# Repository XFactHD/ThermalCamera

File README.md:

# ThermalCamera
 Simple MLX90640 based thermal camera

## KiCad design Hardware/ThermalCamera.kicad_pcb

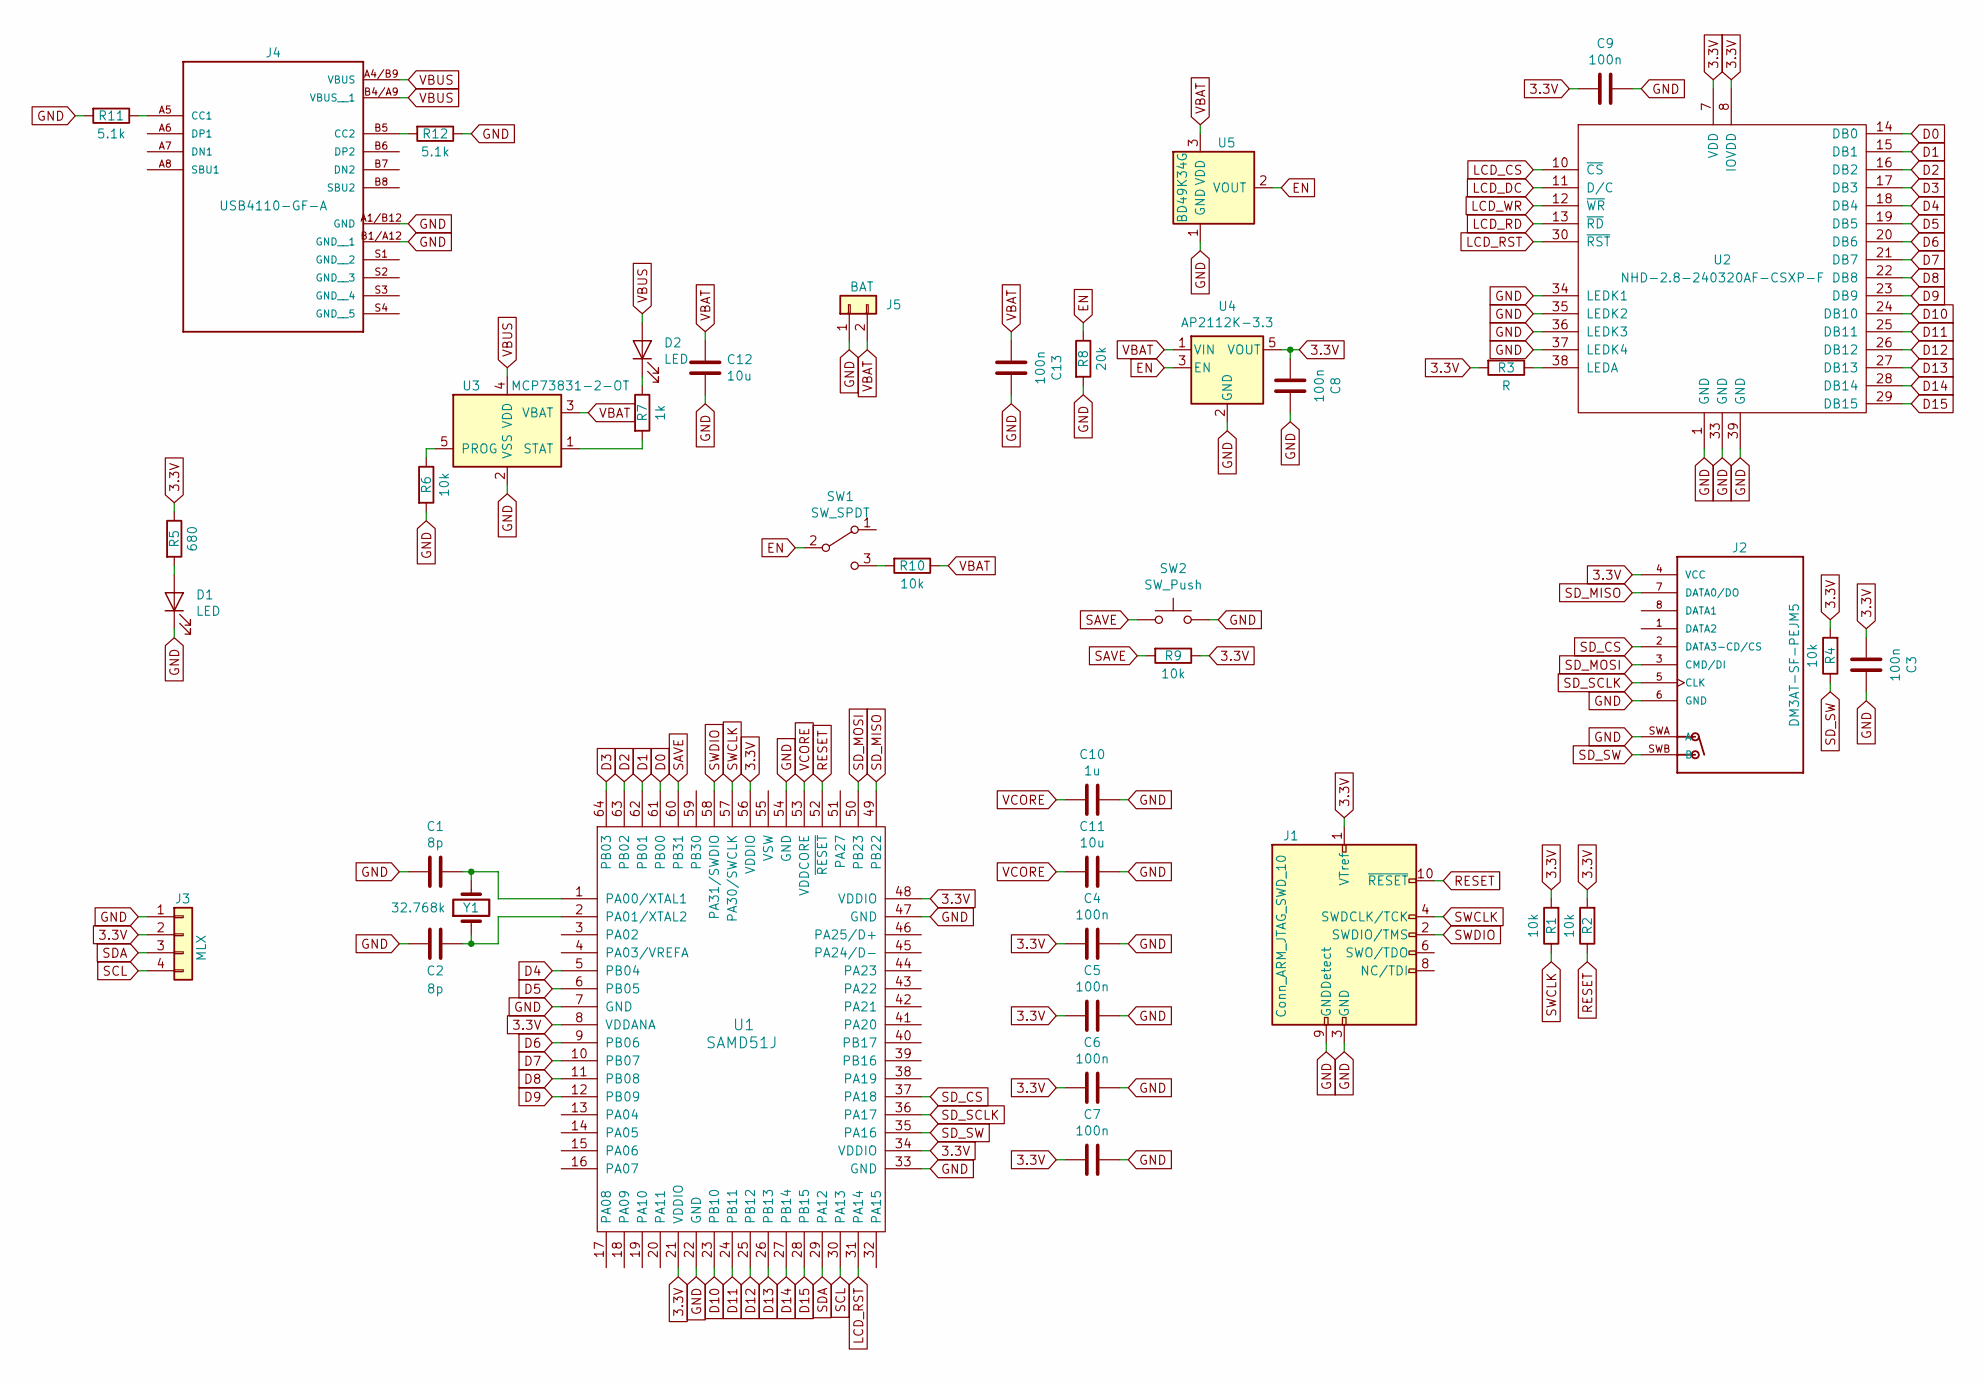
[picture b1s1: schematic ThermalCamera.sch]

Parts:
C1, C2: 8p; C_0805
C3, C4, C5, C6, C7, C8, C9, C13: 100n; C_0805
C10: 1u; C_0805
C11, C12: 10u; C_0805
D1, D2: LED; LED_0805
J1: Conn_ARM_JTAG_SWD_10; Pin_Header_Straight_2x05_Pitch1.27mm_SMD
J2: DM3AT-SF-PEJM5; HRS_DM3AT-SF-PEJM5
J3: MLX; JST_SH_SM04B-SRSS-TB_04x1.00mm_Angled
J4: USB4110-GF-A; GCT_USB4110-GF-A
J5: BAT; JST_PH_S2B-PH-SM4-TB_02x2.00mm_Angled
R1, R2, R4, R6, R9, R10: 10k; R_0805
R3: R; R_0805
R5: 680; R_0805
R7: 1k; R_0805
R8: 20k; R_0805
R11, R12: 5.1k; R_0805
SW1: SW_SPDT; SW_SPDT_PCM12
SW2: SW_Push; SW_SPST_B3U-3000P
U1: SAMD51J; TQFP-64_10x10mm_Pitch0.5mm
U2: NHD-2.8-240320AF-CSXP-F
U3: MCP73831-2-OT; SOT-23-5
U4: AP2112K-3.3; SOT-23-5
U5: BD49K34G; SOT-23
Y1: 32.768k; Crystal_SMD_3215-2pin_3.2x1.5mm

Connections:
3.3V: C3.2, C4.2, C5.2, C6.2, C7.2, C8.2, C9.2, J1.1 (VTref), J2.4 (VCC), J3.2, R1.2, R2.2, R3.2, R4.2, R5.1, R9.1, U1.8 (VDDANA), U1.21 (VDDIO), U1.34 (VDDIO), U1.48 (VDDIO), U1.56 (VDDIO), U2.7 (VDD), U2.8 (IOVDD), U4.5 (VOUT)
D0: U1.61 (PB00), U2.14 (DB0)
D1: U1.62 (PB01), U2.15 (DB1)
D2: U1.63 (PB02), U2.16 (DB2)
D3: U1.64 (PB03), U2.17 (DB3)
D4: U1.5 (PB04), U2.18 (DB4)
D5: U1.6 (PB05), U2.19 (DB5)
D6: U1.9 (PB06), U2.20 (DB6)
D7: U1.10 (PB07), U2.21 (DB7)
D8: U1.11 (PB08), U2.22 (DB8)
D9: U1.12 (PB09), U2.23 (DB9)
D10: U1.23 (PB10), U2.24 (DB10)
D11: U1.24 (PB11), U2.25 (DB11)
D12: U1.25 (PB12), U2.26 (DB12)
D13: U1.26 (PB13), U2.27 (DB13)
D14: U1.27 (PB14), U2.28 (DB14)
D15: U1.28 (PB15), U2.29 (DB15)
EN: R8.1, SW1.2 (B), U4.3 (EN), U5.2 (VOUT)
GND: C1.2, C2.2, C3.1, C4.1, C5.1, C6.1, C7.1, C8.1, C9.1, C10.1, C11.1, C12.1, C13.1, D1.1 (K), J1.3 (GND), J1.5 (GND), J1.9 (GNDDetect), J2.6 (GND), J2.SWA (A), J3.1, J4.A1/B12 (GND), J4.B1/A12 (GND__1), J5.1, R6.2, R8.2, R11.2, R12.1, SW2.2, U1.7 (GND), U1.22 (GND), U1.33 (GND), U1.47 (GND), U1.54 (GND), U2.1 (GND), U2.33 (GND), U2.34 (LEDK1), U2.35 (LEDK2), U2.36 (LEDK3), U2.37 (LEDK4), U2.39 (GND), U3.2 (VSS), U4.2 (GND), U5.1 (GND)
LCD_CS: U2.10 (~CS)
LCD_DC: U2.11 (D/C)
LCD_RD: U2.13 (~RD)
LCD_RST: U1.31 (PA14), U2.30 (~RST)
LCD_WR: U2.12 (~WR)
unnamed: C1.1, U1.1 (PA00/XTAL1), Y1.2
unnamed: C2.1, U1.2 (PA01/XTAL2), Y1.1
unnamed: D1.2 (A), R5.2
unnamed: D2.1 (K), R7.1
unnamed: J4.A5 (CC1), R11.1
unnamed: J4.B5 (CC2), R12.2
unnamed: R3.1, U2.38 (LEDA)
unnamed: R6.1, U3.5 (PROG)
unnamed: R7.2, U3.1 (STAT)
unnamed: R10.2, SW1.3 (C)
RESET: J1.10 (~RESET~), R2.1, U1.52 (~RESET)
SAVE: R9.2, SW2.1, U1.60 (PB31)
SCL: J3.4, U1.30 (PA13)
SDA: J3.3, U1.29 (PA12)
SD_CS: J2.2 (DATA3-CD/CS), U1.37 (PA18)
SD_MISO: J2.7 (DATA0/DO), U1.49 (PB22)
SD_MOSI: J2.3 (CMD/DI), U1.50 (PB23)
SD_SCLK: J2.5 (CLK), U1.36 (PA17)
SD_SW: J2.SWB (B), R4.1, U1.35 (PA16)
SWCLK: J1.4 (SWDCLK/TCK), R1.1, U1.57 (PA30/SWCLK)
SWDIO: J1.2 (SWDIO/TMS), U1.58 (PA31/SWDIO)
VBAT: C12.2, C13.2, J5.2, R10.1, U3.3 (VBAT), U4.1 (VIN), U5.3 (VDD)
VBUS: D2.2 (A), J4.A4/B9 (VBUS), J4.B4/A9 (VBUS__1), U3.4 (VDD)
VCORE: C10.2, C11.2, U1.53 (VDDCORE)

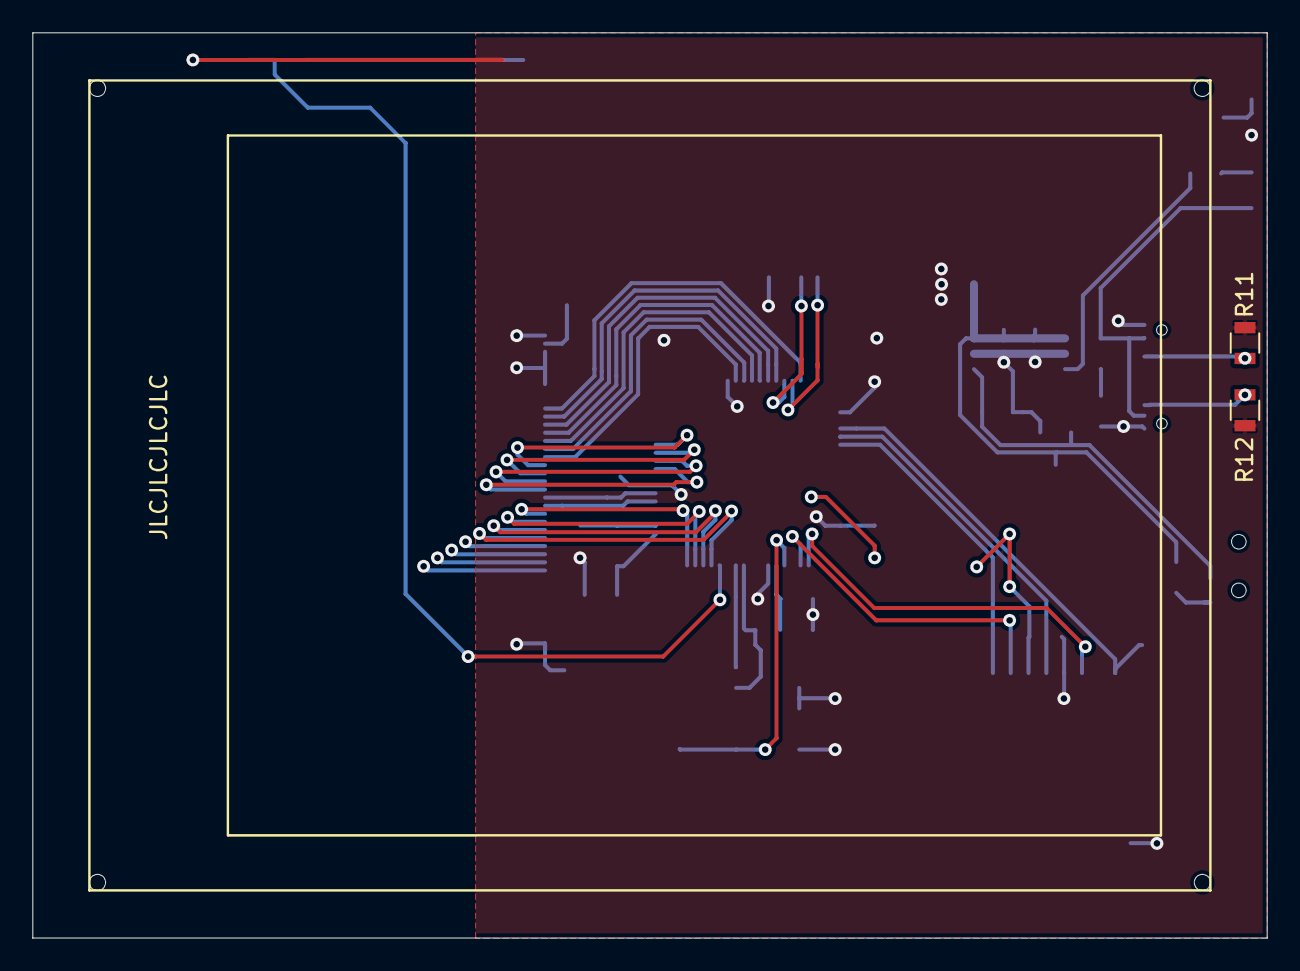
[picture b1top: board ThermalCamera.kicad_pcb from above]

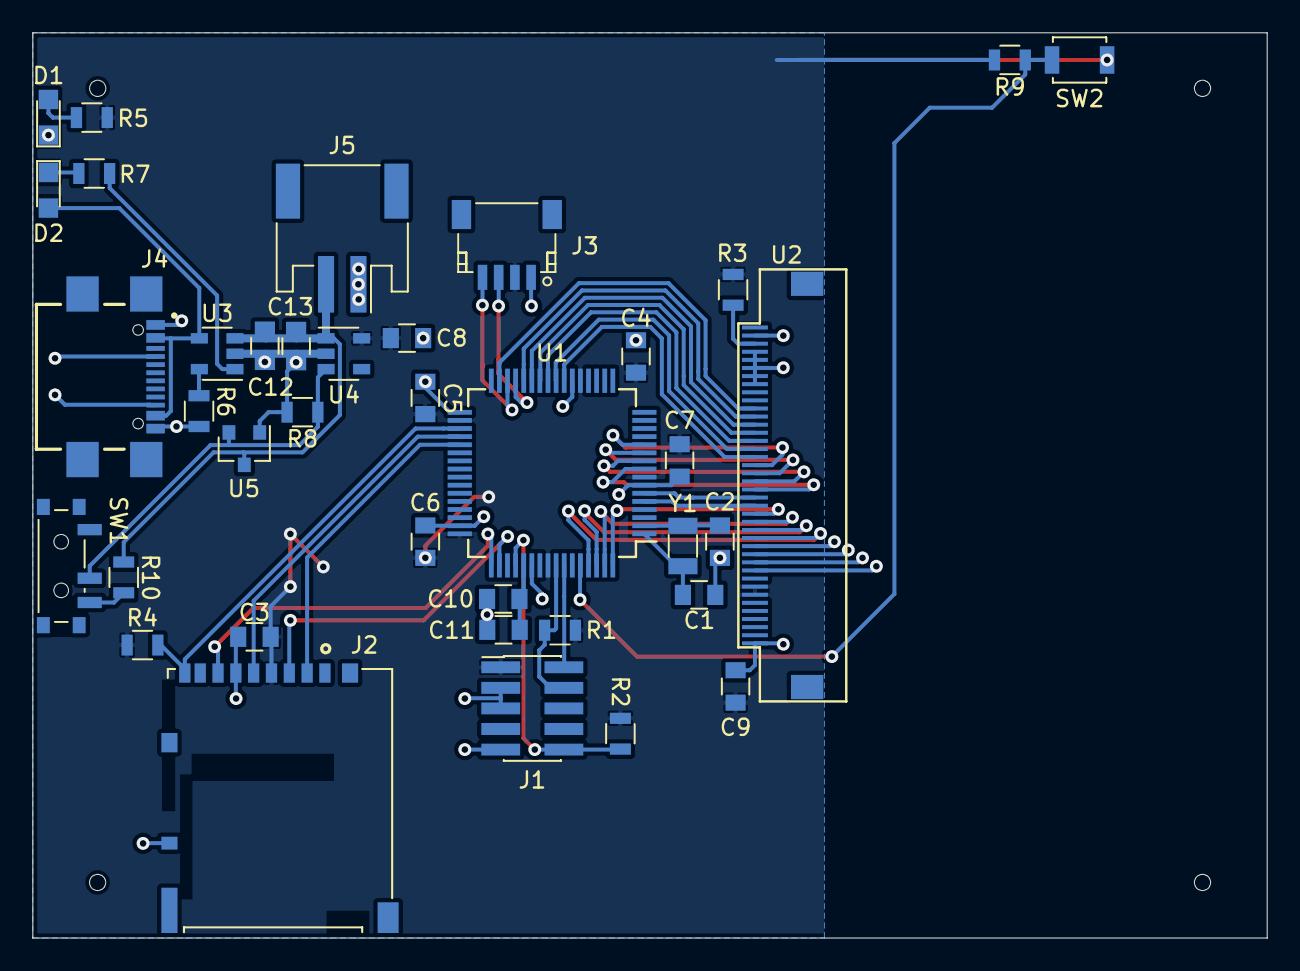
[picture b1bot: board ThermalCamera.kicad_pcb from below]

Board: 2 copper layers, 76.2 x 55.9 mm, 40 parts (37 on the bottom side), 44 nets.
